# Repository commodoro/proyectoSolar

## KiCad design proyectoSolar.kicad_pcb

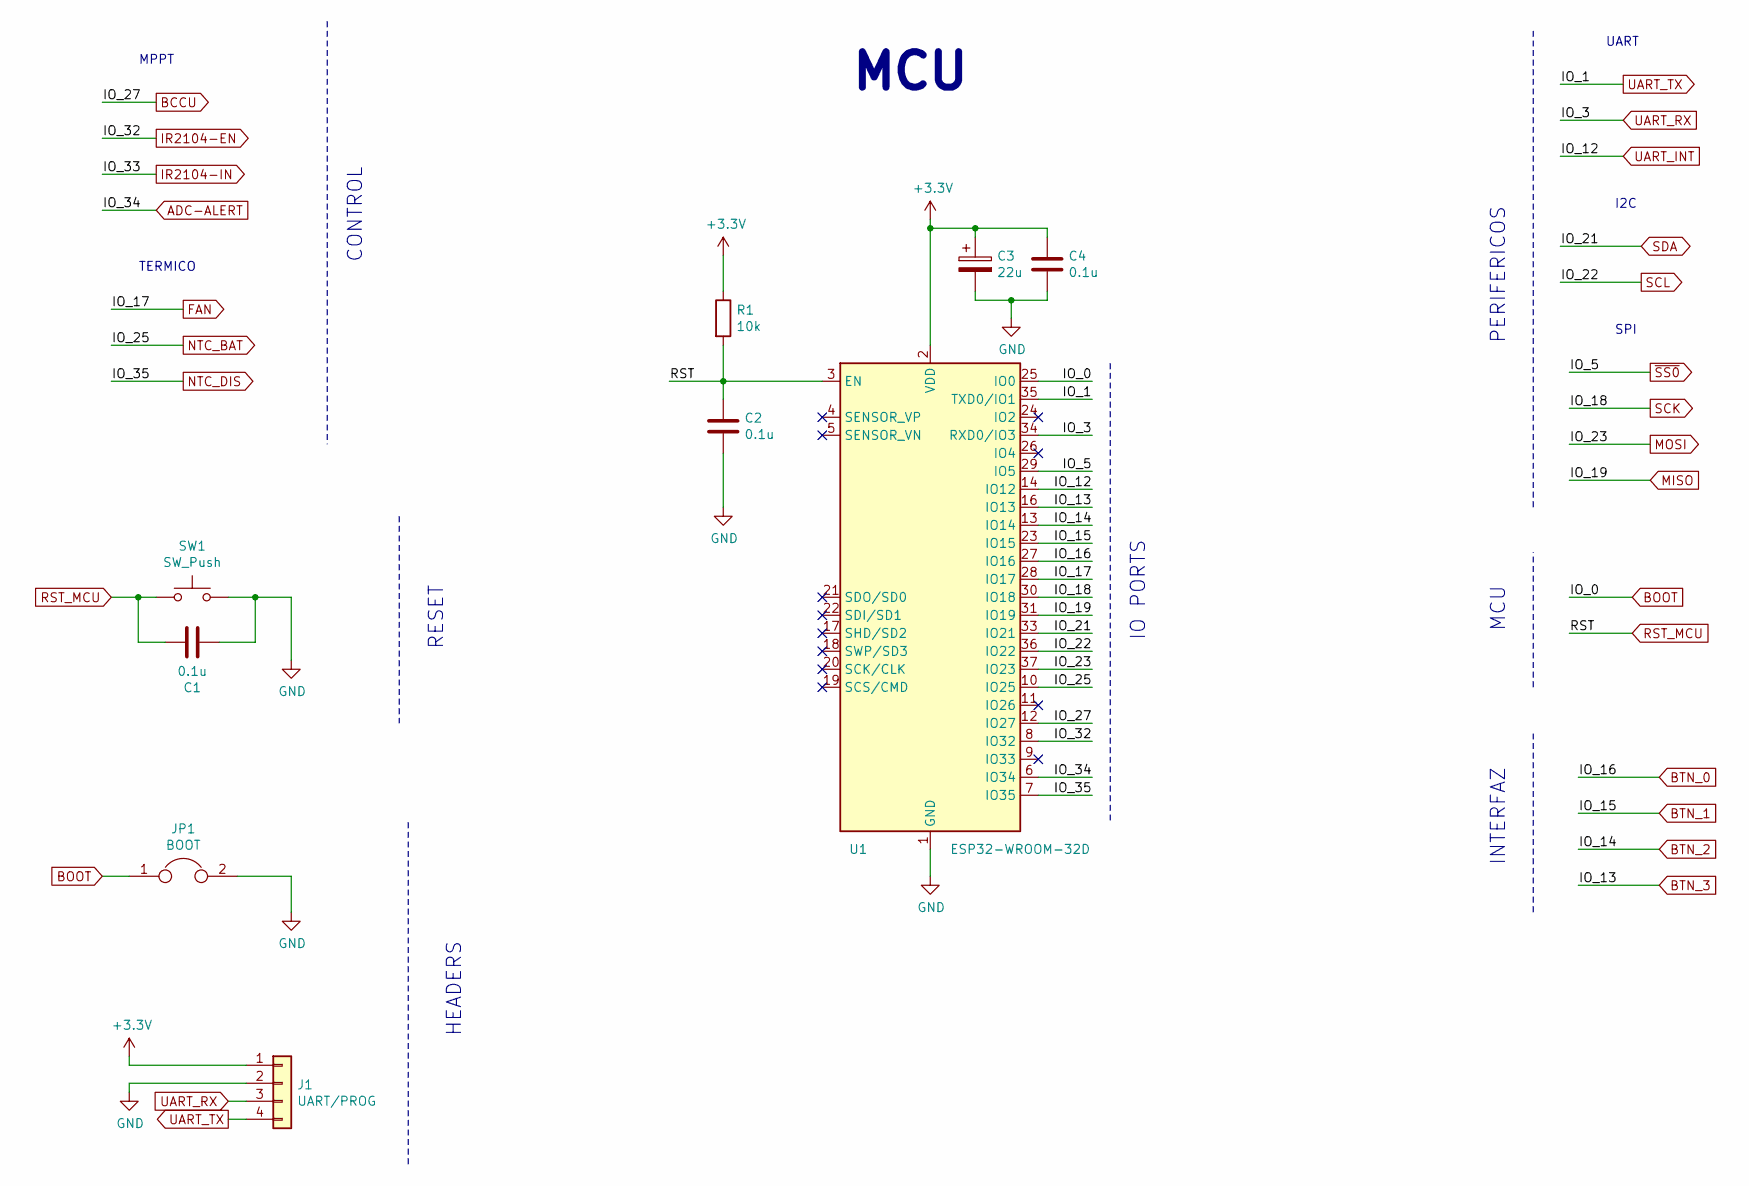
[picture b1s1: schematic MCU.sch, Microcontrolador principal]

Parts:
C1, C2, C4: 0.1u; C_0603
C3: 22u; CP_Elec_5x4.5
J1: UART/PROG; Pin_Header_Straight_1x04_Pitch2.54mm
JP1: BOOT; Pin_Header_Straight_1x02_Pitch2.54mm
R1: 10k; R_0603
SW1: SW_Push; SW_SPST_B3U-1000P
U1: ESP32-WROOM-32D; ESP32-WROOM

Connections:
+3V3: C3.1, C4.1, J1.1, R1.1, U1.2 (VDD); also elsewhere on the board
ADC-ALERT: U1.6 (IO34); also elsewhere on the board
BCCU: U1.12 (IO27); also elsewhere on the board
BOOT: JP1.1, U1.25 (IO0)
BTN_0: U1.27 (IO16); also elsewhere on the board
BTN_1: U1.23 (IO15); also elsewhere on the board
BTN_2: U1.13 (IO14); also elsewhere on the board
BTN_3: U1.16 (IO13); also elsewhere on the board
FAN: U1.28 (IO17)
GND: C1.1, C2.2, C3.2, C4.2, J1.2, JP1.2, SW1.2, U1.1 (GND), U1.15 (GND), U1.38 (GND), U1.39 (GND); also elsewhere on the board
IR2104-EN: U1.8 (IO32); also elsewhere on the board
MISO: U1.31 (IO19); also elsewhere on the board
MOSI: U1.37 (IO23); also elsewhere on the board
NTC_BAT: U1.10 (IO25)
NTC_DIS: U1.7 (IO35)
RST_MCU: C1.2, C2.1, R1.2, SW1.1, U1.3 (EN)
SCK: U1.30 (IO18); also elsewhere on the board
SCL: U1.36 (IO22); also elsewhere on the board
SDA: U1.33 (IO21); also elsewhere on the board
UART_INT: U1.14 (IO12); also elsewhere on the board
UART_RX: J1.3, U1.34 (RXD0/IO3); also elsewhere on the board
UART_TX: J1.4, U1.35 (TXD0/IO1); also elsewhere on the board
~SS0: U1.29 (IO5); also elsewhere on the board

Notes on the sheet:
UART
SPI
I2C
TERMICO
MPPT
IO PORTS
CONTROL
HEADERS
RESET
PERIFERICOS
MCU
INTERFAZ

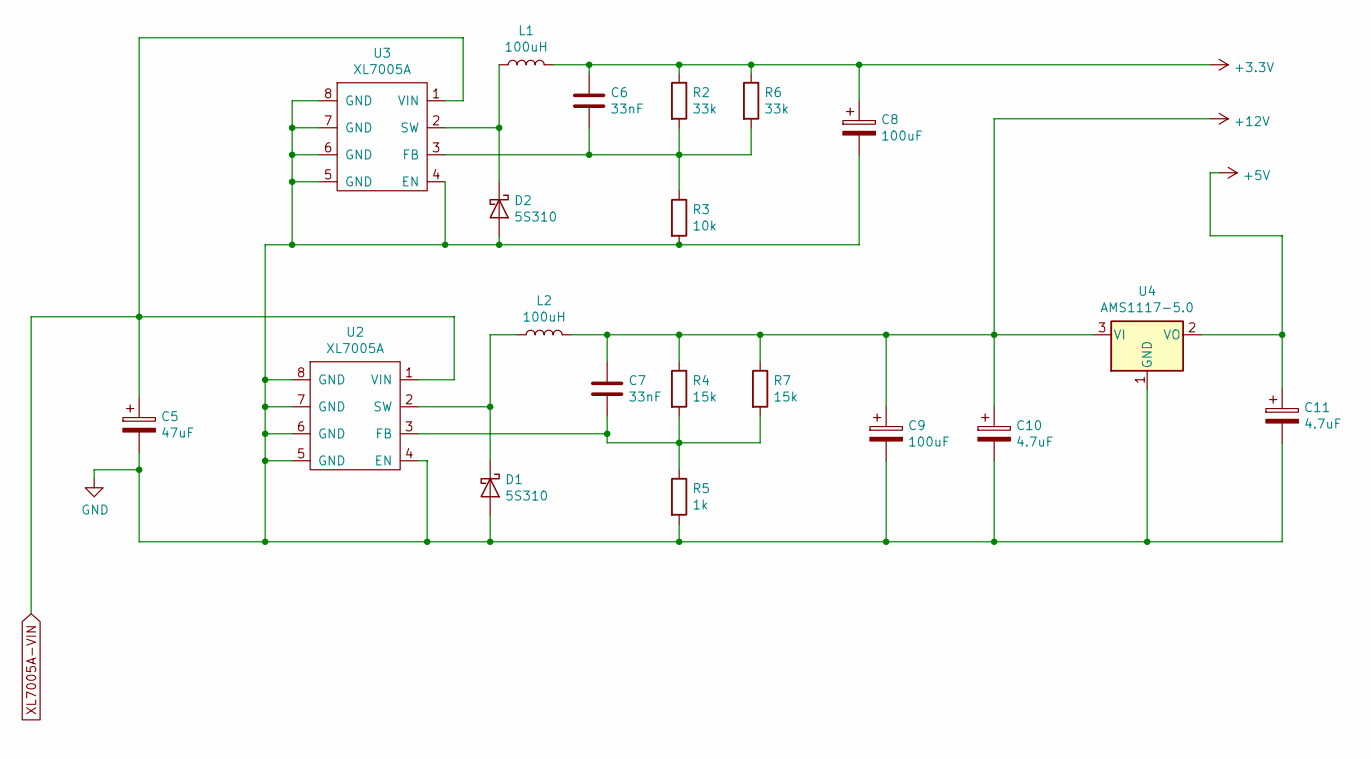
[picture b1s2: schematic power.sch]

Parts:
C5: 47uF; CP_Elec_5x4.5
C6, C7: 33nF; C_0603
C8, C9: 100uF; CP_Elec_5x4.5
C10, C11: 4.7uF; CP_Elec_3x5.3
D1, D2: 5S310; D_SOD-123
L1, L2: 100uH; L_7.3x7.3_H3.5
R2, R6: 33k; R_0603
R3: 10k; R_0603
R4, R7: 15k; R_0603
R5: 1k; R_0603
U2, U3: XL7005A; SOIC-8-1EP_3.9x4.9mm_Pitch1.27mm
U4: AMS1117-5.0; SOT-223-3_TabPin2

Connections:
+3V3: C6.1, C8.1, L1.2, R2.1, R6.1; also elsewhere on the board
+5V: C11.1, U4.2 (VO); also elsewhere on the board
+12V: C7.1, C9.1, C10.1, L2.2, R4.1, R7.1, U4.3 (VI); also elsewhere on the board
GND: C5.2, C8.2, C9.2, C10.2, C11.2, D1.2 (A), D2.2 (A), R3.2, R5.2, U2.4 (EN), U2.5 (GND), U2.6 (GND), U2.7 (GND), U2.8 (GND), U2.9, U3.4 (EN), U3.5 (GND), U3.6 (GND), U3.7 (GND), U3.8 (GND), U3.9, U4.1 (GND); also elsewhere on the board
unnamed: C6.2, R2.2, R3.1, R6.2, U3.3 (FB)
unnamed: C7.2, R4.2, R5.1, R7.2, U2.3 (FB)
unnamed: D1.1 (K), L2.1, U2.2 (SW)
unnamed: D2.1 (K), L1.1, U3.2 (SW)
XL7005A-VIN: C5.1, U2.1 (VIN), U3.1 (VIN)

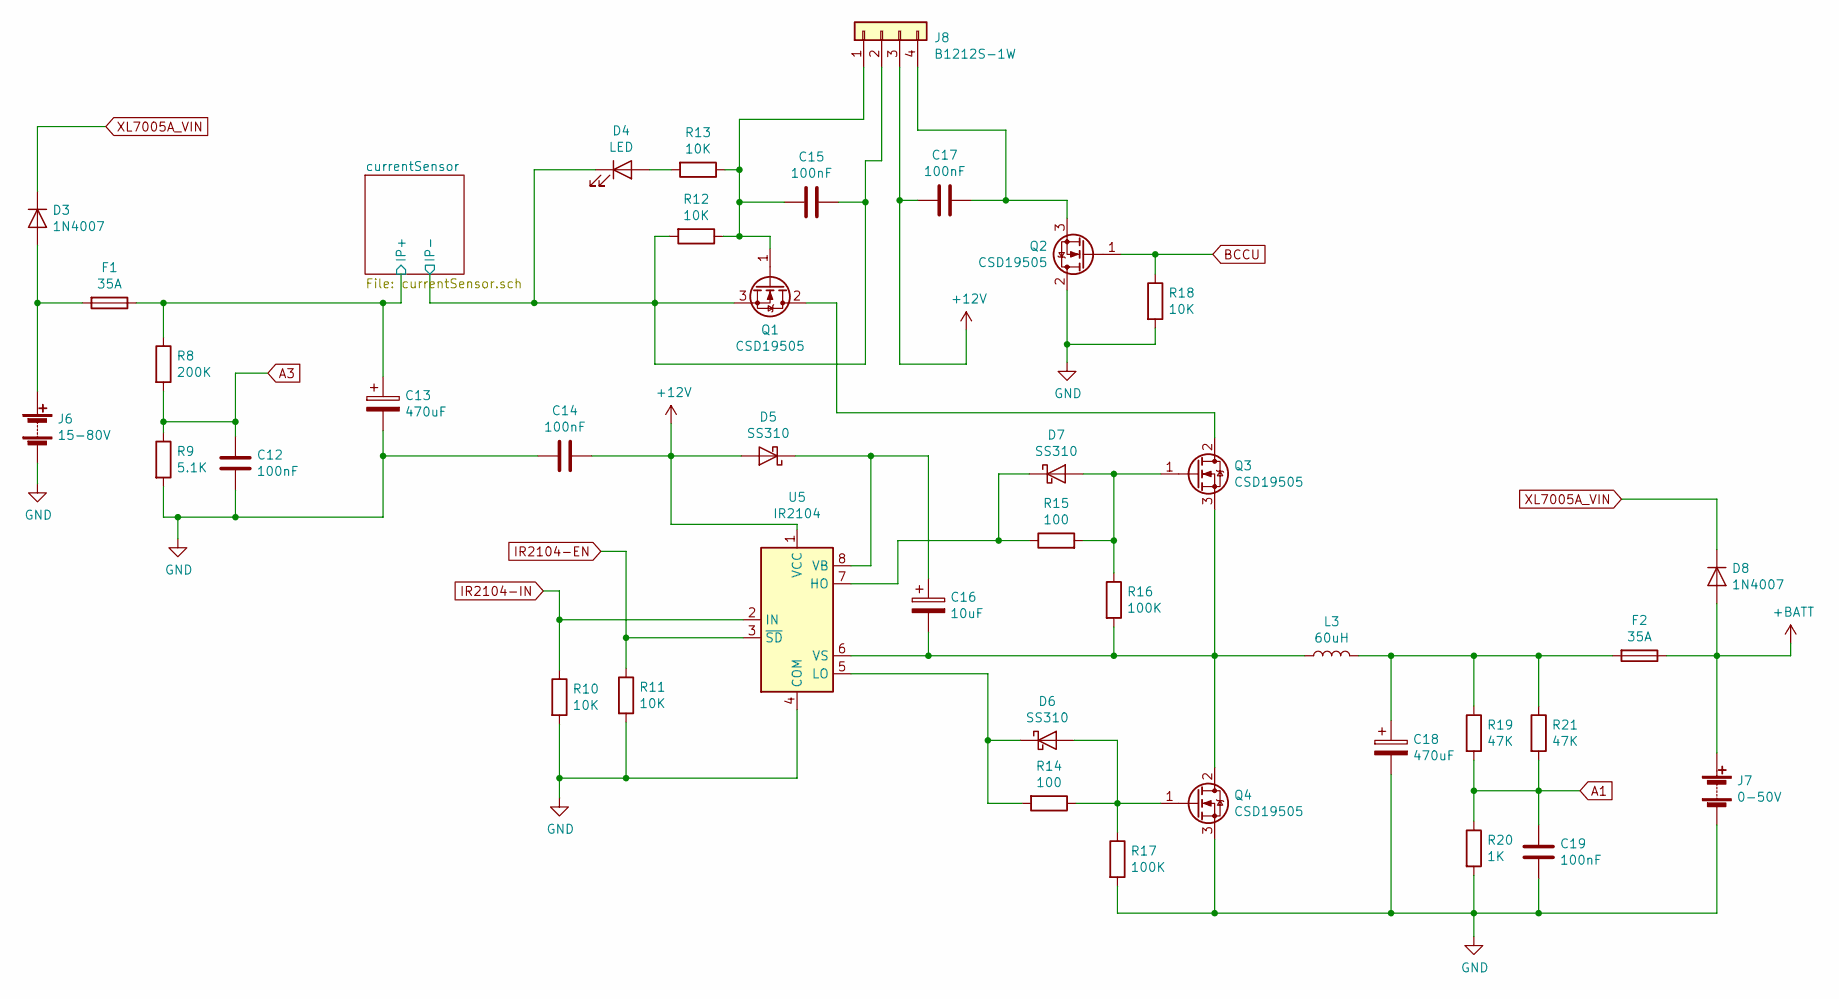
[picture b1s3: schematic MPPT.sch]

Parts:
C12, C14, C15, C17, C19: 100nF; C_0603
C13, C18: 470uF; CP_Elec_6.3x4.5
C16: 10uF; CP_Elec_3x5.3
D3, D8: 1N4007; D_SOD-123
D4: LED; D_0603
D5, D6, D7: SS310; D_SOD-123
F1, F2: 35A; BladeFuse-CarType
J6: 15-80V; SolderWirePad_2x_1-5mmDrill
J7: 0-50V; SolderWirePad_2x_1-5mmDrill
J8: B1212S-1W; Pin_Header_Straight_1x04_Pitch2.54mm
L3: 60uH; L_Toroid_Vertical_L28.6mm_W14.3mm_P11.43mm_Bourns_5700
Q1, Q2, Q3, Q4: CSD19505; TO-220-3_Vertical
R8: 200K; R_0603
R9: 5.1K; R_0603
R10, R11, R12, R13, R18: 10K; R_0603
R14, R15: 100; R_0603
R16, R17: 100K; R_0603
R19, R21: 47K; R_0603
R20: 1K; R_0603
U5: IR2104; SOIC-8_3.9x4.9mm_Pitch1.27mm

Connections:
+12V: C14.1, C17.2, D5.2 (A), J8.3, U5.1 (VCC); also elsewhere on the board
+BATT: D8.2 (A), F2.1, J7.1 (+); also elsewhere on the board
/MPPT/currentSensor/IP+: C13.1, F1.1, R8.1; also elsewhere on the board
/MPPT/currentSensor/IP-: C15.1, D4.1 (K), J8.2, Q1.3 (S), R12.2; also elsewhere on the board
A1: C19.1, R19.2, R20.1, R21.2; also elsewhere on the board
A3: C12.2, R8.2, R9.1; also elsewhere on the board
BCCU: Q2.1 (G), R18.1; also elsewhere on the board
GND: C12.1, C13.2, C14.2, C18.2, C19.2, J6.2 (-), J7.2 (-), Q2.2 (D), Q4.3 (S), R9.2, R10.2, R11.2, R17.2, R18.2, R20.2, U5.4 (COM); also elsewhere on the board
IR2104-EN: R11.1, U5.3 (~SD); also elsewhere on the board
IR2104-IN: R10.1, U5.2 (IN)
unnamed: C15.2, J8.1, Q1.1 (G), R12.1, R13.1
unnamed: C16.1, D5.1 (K), U5.8 (VB)
unnamed: C16.2, L3.1, Q3.3 (S), Q4.2 (D), R16.2, U5.6 (VS)
unnamed: C17.1, J8.4, Q2.3 (S)
unnamed: C18.1, F2.2, L3.2, R19.1, R21.1
unnamed: D3.2 (A), F1.2, J6.1 (+)
unnamed: D4.2 (A), R13.2
unnamed: D6.1 (K), R14.2, U5.5 (LO)
unnamed: D6.2 (A), Q4.1 (G), R14.1, R17.1
unnamed: D7.1 (K), R15.1, U5.7 (HO)
unnamed: D7.2 (A), Q3.1 (G), R15.2, R16.1
unnamed: Q1.2 (D), Q3.2 (D)
XL7005A_VIN: D3.1 (K), D8.1 (K)

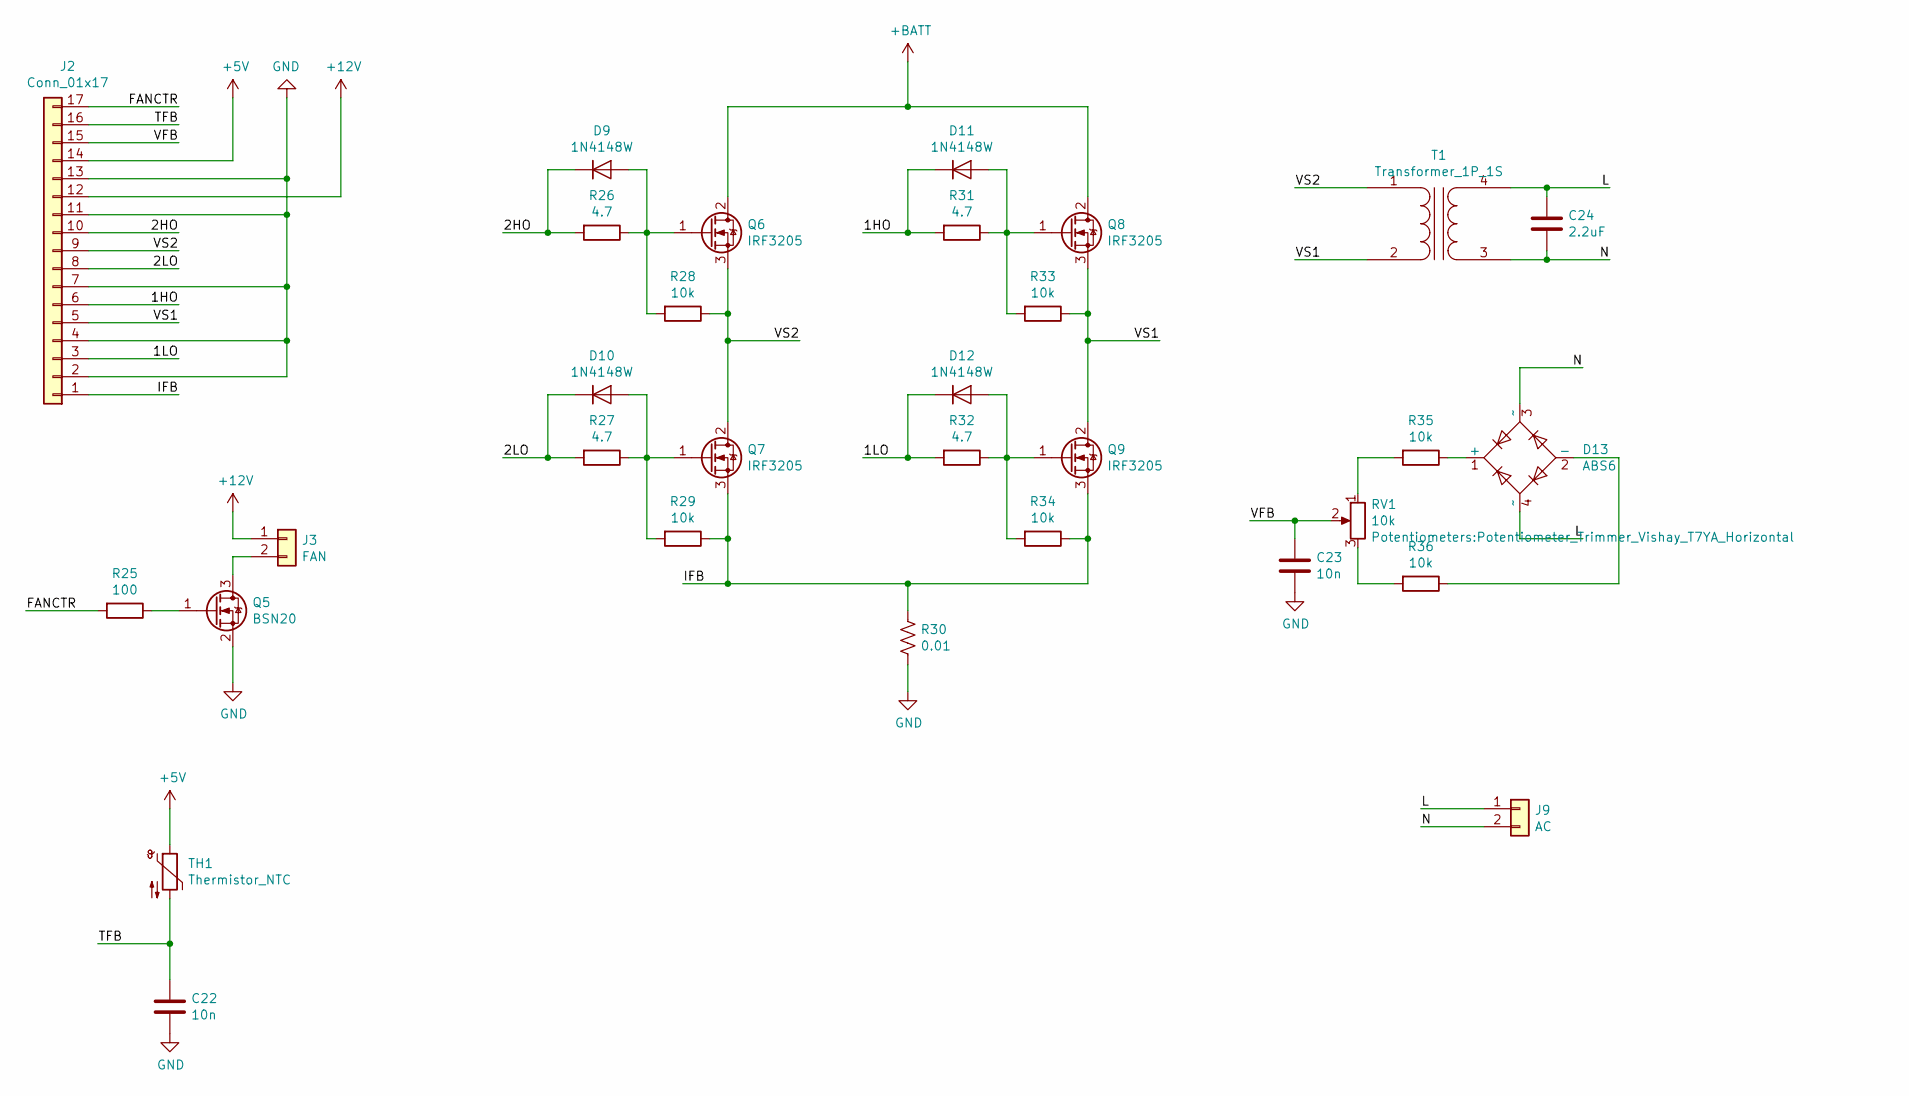
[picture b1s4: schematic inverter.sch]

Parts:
C22, C23: 10n; C_0603
C24: 2.2uF; C_0603
D9, D10, D11, D12: 1N4148W; D_SOD-123
D13: ABS6; Diode_Bridge_DFS
J2: Conn_01x17; Pin_Header_Straight_1x17_Pitch2.54mm
J3: FAN; Pin_Header_Straight_1x02_Pitch2.54mm
J9: AC; SolderWirePad_2x_1-5mmDrill
Q5: BSN20; SOT-23
Q6, Q7, Q8, Q9: IRF3205; TO-220-3_Vertical
R25: 100; R_0603
R26, R27, R31, R32: 4.7; R_0805
R28, R29, R33, R34, R35, R36: 10k; R_0603
R30: 0.01; R_1812
RV1: 10k; Potentiometer_Trimmer_Vishay_T7YA_Horizontal
T1: Transformer_1P_1S; Transformer_CHK_EI38-3VA_1xSec
TH1: Thermistor_NTC; Pin_Header_Straight_1x02_Pitch2.54mm

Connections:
+5V: J2.14, TH1.1; also elsewhere on the board
+12V: J2.12, J3.1; also elsewhere on the board
+BATT: Q6.2 (D), Q8.2 (D); also elsewhere on the board
/inverter/1HO: D11.1 (K), J2.6, R31.2
/inverter/1LO: D12.1 (K), J2.3, R32.2
/inverter/2HO: D9.1 (K), J2.10, R26.2
/inverter/2LO: D10.1 (K), J2.8, R27.2
/inverter/FANCTR: J2.17, R25.2
/inverter/IFB: J2.1, Q7.3 (S), Q9.3 (S), R29.1, R30.1, R34.1
/inverter/L: C24.1, D13.4 (~~), J9.1, T1.4 (SB)
/inverter/N: C24.2, D13.3 (~~), J9.2, T1.3 (SA)
/inverter/TFB: C22.1, J2.16, TH1.2
/inverter/VFB: C23.1, J2.15, RV1.2
/inverter/VS1: J2.5, Q8.3 (S), Q9.2 (D), R33.1, T1.2 (AB)
/inverter/VS2: J2.9, Q6.3 (S), Q7.2 (D), R28.1, T1.1 (AA)
GND: C22.2, C23.2, J2.2, J2.4, J2.7, J2.11, J2.13, Q5.2 (S), R30.2; also elsewhere on the board
unnamed: D9.2 (A), Q6.1 (G), R26.1, R28.2
unnamed: D10.2 (A), Q7.1 (G), R27.1, R29.2
unnamed: D11.2 (A), Q8.1 (G), R31.1, R33.2
unnamed: D12.2 (A), Q9.1 (G), R32.1, R34.2
unnamed: D13.1 (+), R35.1
unnamed: D13.2 (-), R36.1
unnamed: J3.2, Q5.3 (D)
unnamed: Q5.1 (G), R25.1
unnamed: R35.2, RV1.1
unnamed: R36.2, RV1.3

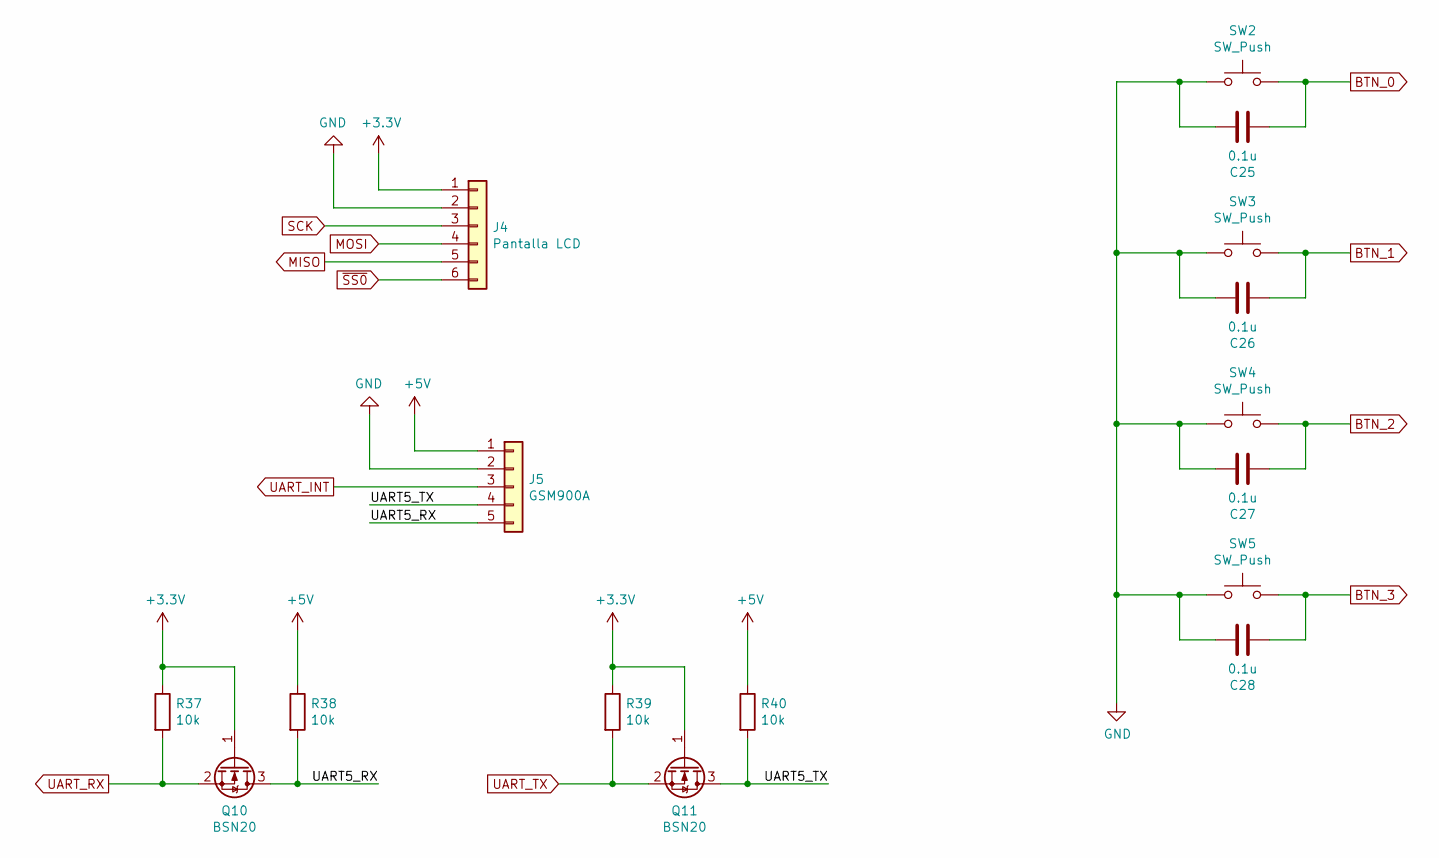
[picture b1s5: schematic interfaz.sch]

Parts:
C25, C26, C27, C28: 0.1u; C_0603
J4: Pantalla LCD; Pin_Header_Straight_1x06_Pitch2.54mm
J5: GSM900A; Pin_Header_Straight_1x05_Pitch2.54mm
Q10, Q11: BSN20; SOT-23
R37, R38, R39, R40: 10k; R_0603
SW2, SW3, SW4, SW5: SW_Push; Pin_Header_Straight_1x02_Pitch2.54mm

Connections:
+3V3: J4.1, Q10.1 (G), Q11.1 (G), R37.1, R39.1; also elsewhere on the board
+5V: J5.1, R38.1, R40.1; also elsewhere on the board
/interfaz/UART5_RX: J5.5, Q10.3 (D), R38.2
/interfaz/UART5_TX: J5.4, Q11.3 (D), R40.2
BTN_0: C25.1, SW2.2; also elsewhere on the board
BTN_1: C26.1, SW3.2; also elsewhere on the board
BTN_2: C27.1, SW4.2; also elsewhere on the board
BTN_3: C28.1, SW5.2; also elsewhere on the board
GND: C25.2, C26.2, C27.2, C28.2, J4.2, J5.2, SW2.1, SW3.1, SW4.1, SW5.1; also elsewhere on the board
MISO: J4.5; also elsewhere on the board
MOSI: J4.4; also elsewhere on the board
SCK: J4.3; also elsewhere on the board
UART_INT: J5.3; also elsewhere on the board
UART_RX: Q10.2 (S), R37.2; also elsewhere on the board
UART_TX: Q11.2 (S), R39.2; also elsewhere on the board
~SS0: J4.6; also elsewhere on the board

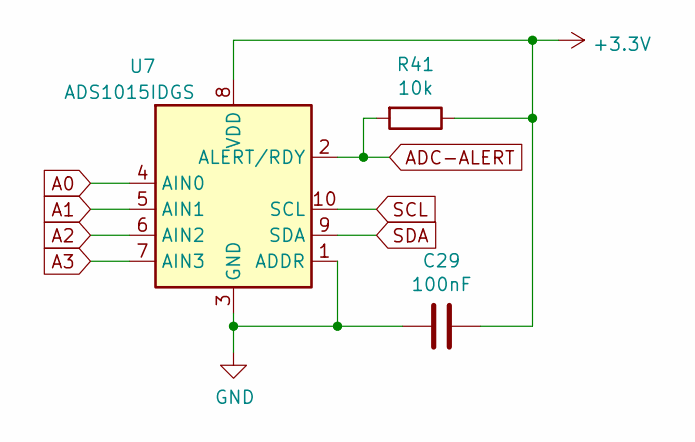
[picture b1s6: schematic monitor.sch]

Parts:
C29: 100nF; C_0603
R41: 10k; R_0603
U7: ADS1015IDGS; MSOP-10_3x3mm_Pitch0.5mm

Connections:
+3V3: C29.1, R41.1, U7.8 (VDD); also elsewhere on the board
A0: U7.4 (AIN0)
A1: U7.5 (AIN1); also elsewhere on the board
A2: U7.6 (AIN2); also elsewhere on the board
A3: U7.7 (AIN3); also elsewhere on the board
ADC-ALERT: R41.2, U7.2 (ALERT/RDY); also elsewhere on the board
GND: C29.2, U7.1 (ADDR), U7.3 (GND); also elsewhere on the board
SCL: U7.10 (SCL); also elsewhere on the board
SDA: U7.9 (SDA); also elsewhere on the board

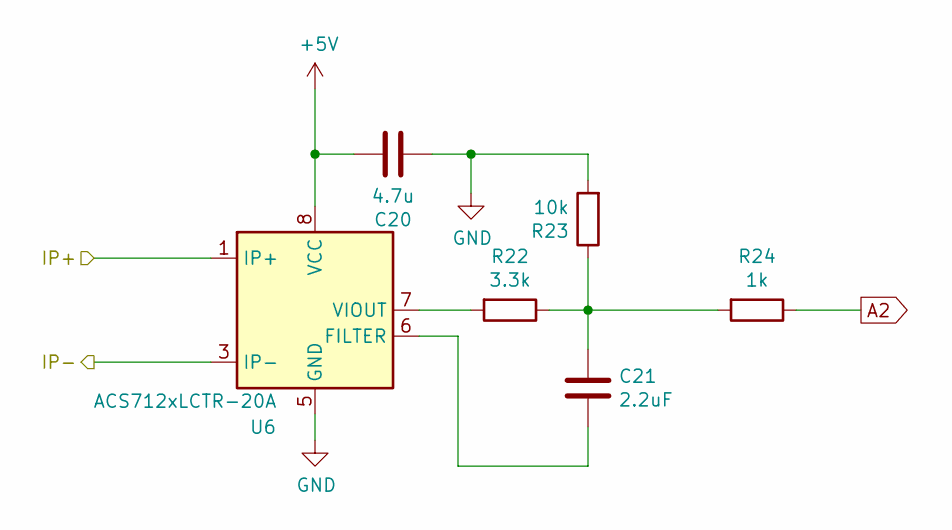
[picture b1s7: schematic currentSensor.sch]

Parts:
C20: 4.7u; CP_Elec_3x5.3
C21: 2.2uF; C_0603
R22: 3.3k; R_0603
R23: 10k; R_0603
R24: 1k; R_0603
U6: ACS712xLCTR-20A; SOIC-8_3.9x4.9mm_Pitch1.27mm

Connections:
+5V: C20.1, U6.8 (VCC); also elsewhere on the board
/MPPT/currentSensor/IP+: U6.1 (IP+), U6.2 (IP+); also elsewhere on the board
/MPPT/currentSensor/IP-: U6.3 (IP-), U6.4 (IP-); also elsewhere on the board
A2: R24.1; also elsewhere on the board
GND: C20.2, R23.2, U6.5 (GND); also elsewhere on the board
unnamed: C21.1, U6.6 (FILTER)
unnamed: C21.2, R22.1, R23.1, R24.2
unnamed: R22.2, U6.7 (VIOUT)

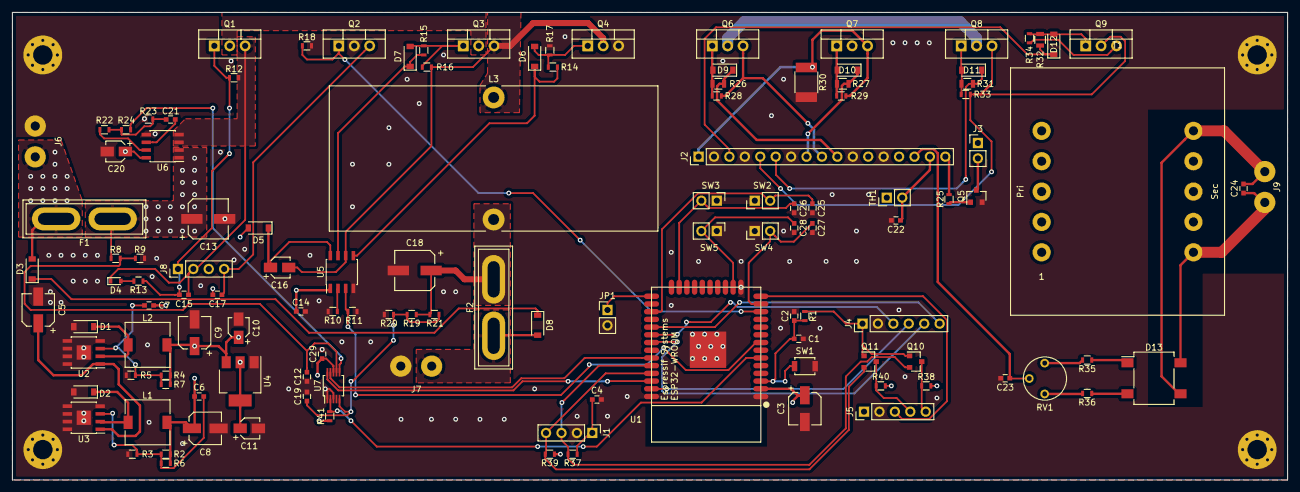
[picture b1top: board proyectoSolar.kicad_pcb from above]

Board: 4 copper layers, 210.0 x 77.0 mm, 124 parts (0 on the bottom side), 74 nets.

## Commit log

2021-10-11 Primer commit
2021-10-11 he añadido archivo de texto
2021-10-11 Trabajo dia 1, micro organizado
2021-10-15 Actualizado 15/10
2021-10-17 Update monitor.sch
    He actualizado la hoja Monitor
2021-10-18 Trabajo de Carmen y Javi
2021-10-18 Actualizada y arreglada librería de componentes
2021-12-11 Esquemático acabado y asignación de huellas
2021-12-19 Modelos 3D dificiles incluidos
2021-12-19 Punto restauracion 18:29
2021-12-19 Todo en su sitio
2021-12-19 Punto de control pistas
2021-12-20 Acabado
2021-12-20 Imagenes
